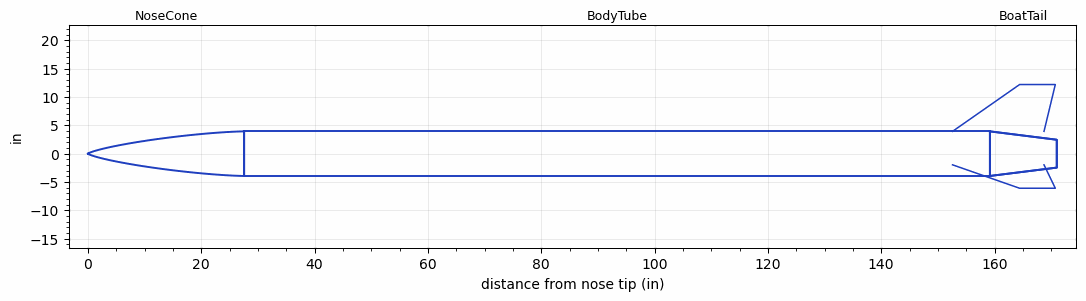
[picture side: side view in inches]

<RASAeroDocument>
 <FileVersion>2</FileVersion>
 <RocketDesign>
  <NoseCone>
   <Length>27.56</Length>
   <Diameter>7.87</Diameter>
   <Shape>Von Karman Ogive</Shape>
   <Location>0</Location>
  </NoseCone>
  <BodyTube>
   <Length>131.63</Length>
   <Diameter>7.87</Diameter>
   <Location>27.56</Location>
   <BoattailLength>11.8</BoattailLength>
   <BoattailRearDiameter>4.92</BoattailRearDiameter>
   <Overhang>9.546999</Overhang>
   <Fin>
    <Count>3</Count>
    <Chord>16.147</Chord>
    <Span>8.27</Span>
    <SweepDistance>11.84</SweepDistance>
    <TipChord>6.3</TipChord>
    <Thickness>0.2362</Thickness>
    <Location>6.6</Location>
    <AirfoilSection>Hexagonal</AirfoilSection>
    <FX1>1</FX1>
    <FX3>1</FX3>
   </Fin>
   <Protuberance>
    <StreamlinedNoBaseDrag>1.5</StreamlinedNoBaseDrag>
    <StreamlinedWithBaseDrag>10.5</StreamlinedWithBaseDrag>
    <InclinedPlate1Angle>0</InclinedPlate1Angle>
    <InclinedPlate1FrontalArea>0</InclinedPlate1FrontalArea>
    <InclinedPlate2Angle>0</InclinedPlate2Angle>
    <InclinedPlate2FrontalArea>0</InclinedPlate2FrontalArea>
   </Protuberance>
  </BodyTube>
  <BoatTail>
   <Length>11.8</Length>
   <Diameter>7.87</Diameter>
   <RearDiameter>4.92</RearDiameter>
   <Location>159.19</Location>
  </BoatTail>
  <Surface>Smooth Paint</Surface>
  <ModifiedBarrowman>False</ModifiedBarrowman>
  <Turbulence>False</Turbulence>
  <UseBooster1>False</UseBooster1>
  <UseBooster2>False</UseBooster2>
 </RocketDesign>
 <LaunchSite>
  <Altitude>0</Altitude>
  <Pressure>0</Pressure>
  <RodAngle>6</RodAngle>
  <RodLength>39</RodLength>
  <Temperature>74</Temperature>
  <WindSpeed>9.46</WindSpeed>
 </LaunchSite>
 <Recovery>
  <Altitude1>1000</Altitude1>
  <Altitude2>1000</Altitude2>
  <DeviceType1>None</DeviceType1>
  <DeviceType2>None</DeviceType2>
  <Event1>False</Event1>
  <Event2>False</Event2>
  <Size1>1</Size1>
  <Size2>1</Size2>
  <EventType1>None</EventType1>
  <EventType2>None</EventType2>
  <CD1>1.33</CD1>
  <CD2>1.33</CD2>
 </Recovery>
 <SimulationList>
  <Simulation>
   <SustainerEngine>RL1  (ICLR)</SustainerEngine>
   <SustainerLaunchWt>170.28</SustainerLaunchWt>
   <SustainerNozzleDiameter>3.54</SustainerNozzleDiameter>
   <SustainerCG>101.75</SustainerCG>
   <SustainerIgnitionDelay>0</SustainerIgnitionDelay>
   <Booster1SeparationDelay>0</Booster1SeparationDelay>
   <Booster1IgnitionDelay>0</Booster1IgnitionDelay>
   <IncludeBooster1>False</IncludeBooster1>
   <Booster2Delay>0</Booster2Delay>
   <IncludeBooster2>False</IncludeBooster2>
   <TimetoApogee>40.51921</TimetoApogee>
   <MaxAltitude>26180.62</MaxAltitude>
   <MaxVelocity>1548.262</MaxVelocity>
  </Simulation>
 </SimulationList>
</RASAeroDocument>
